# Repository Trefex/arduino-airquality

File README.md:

arduino-airquality
==================
      
In this project, we are building a mobile Arduino Fio based platform to measure air quality.

We currently have multiple components working correctly with the Arduino Fio:

- [x] GPS sensor - Adafruit Ultimate GPS Breakout v3 and the OpenLog
- [x] Dust sensor - Sharp Optical Dust Sensor
- [x] Humidity and temperature sensor - SHT10 by sensiron/DFRobot
- [x] Carbon monoxide sensor - Parallax CO sensor
- [x] Barometric pressure - BMP085 Barometric Pressure/Temperature/Altitude Sensor

We are working on combining them all into a nice light package.

Still to do:
- [x] Create circuit board sketch and etch it
- [x] Solder everything on board
- [x] Build enclosure

Next version improvements:

1. Use smaller arduino board (Nano?) potentially one with GPS builtin.

2. Decide if we want a 5V board.

3. Use 7.4V LI-ion flat and rechargeable battery pack.

4. Use only one voltage regulator if we stay with 3.3V.

5. Move voltage splitter to monitor voltage to between battery and voltage regulator.

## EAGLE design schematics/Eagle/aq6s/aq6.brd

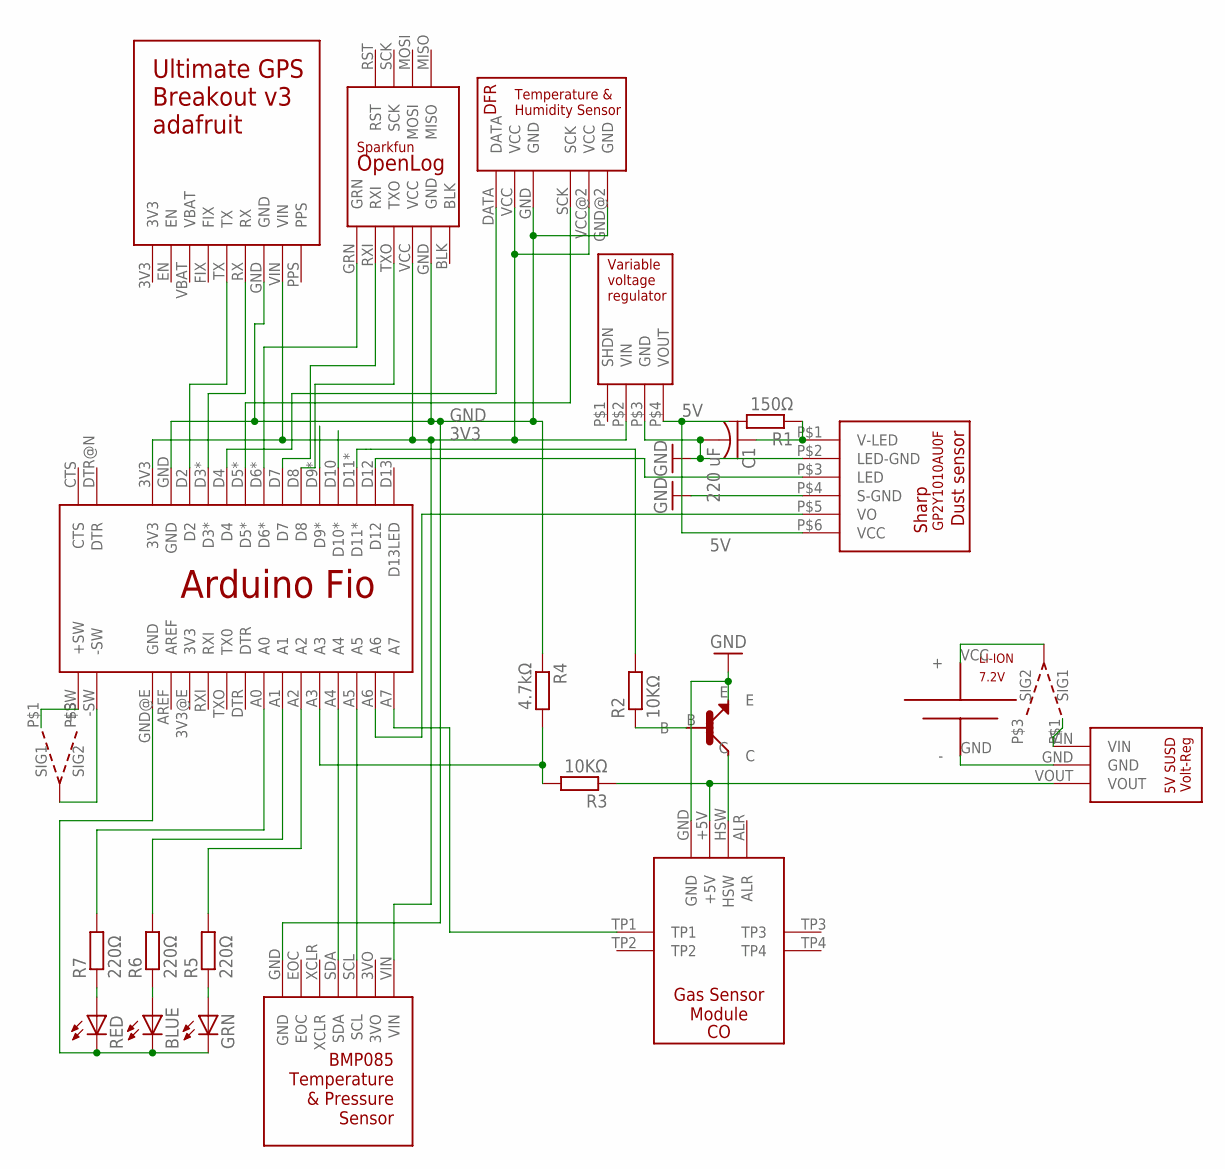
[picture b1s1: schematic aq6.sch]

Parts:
BLUE: LED5MM
C1: 220 uF; C050-025X075
CO: CO; GSM_PARALLAX
GRN: LED5MM
LI-ION: 7.2V; BATTERY_WITH_WIRE_HOLES
R1: 150Ω; 0207/15
R2, R3: 10KΩ; 0204/7
R4: 4.7kΩ; 0204/7
R5, R6, R7: 220Ω; 0204/7
RED: LED5MM
U$1: SHARP_DUST_SENSOR6PIN; 6PIN
U$2: ARDUINO_FIO
U$3: POLOLU_VAR_VOLTAGE_REG
U$4: ADAFRUIT_GPS_V3
U$5: SPARKFUN_OPENLOG
U$6: DFR_TEMP_HUMIDITY
U$7: 5V_SUSD_VOLT_REG
U$8: BMP085
U$10, U$11: SWITCH
U$12: NPN

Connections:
3V3: U$2.3V3, U$3.P$2 (VIN), U$4.VIN, U$5.VCC, U$6.VCC, U$6.VCC@2 (VCC), U$8.VIN
3VO: U$8.3VO
5V: R1.2, U$1.P$6 (VCC), U$3.P$4 (VOUT)
GND: BLUE.K (C), C1.2, CO.GND, GRN.K (C), LI-ION.GND (-), R4.1, RED.K (C), U$1.P$2 (LED-GND), U$1.P$4 (S-GND), U$2.GND, U$2.GND@E (GND), U$3.P$3 (GND), U$4.GND, U$5.GND, U$6.GND, U$6.GND@2 (GND), U$7.GND, U$8.GND, U$12.E
unnamed: U$1.P$3 (LED), U$2.D12
unnamed: C1.1, R1.1, U$1.P$1 (V-LED)
unnamed: U$1.P$5 (VO), U$2.A6
unnamed: U$2.D3*, U$4.RX
unnamed: U$2.D2, U$4.TX
unnamed: U$2.+SW, U$10.P$1 (SIG1)
unnamed: U$2.D6*, U$5.GRN
unnamed: U$2.D7, U$5.RXI
unnamed: U$2.D8, U$5.TXO
unnamed: U$2.-SW, U$10.P$2 (SIG_OUT)
unnamed: LI-ION.VCC (+), U$11.P$2 (SIG_OUT)
unnamed: U$2.D5*, U$6.SCK
unnamed: U$2.D4, U$6.DATA
unnamed: U$7.VIN, U$11.P$1 (SIG1)
unnamed: R5.2, U$2.A2
unnamed: R2.1, U$12.B
unnamed: R2.2, U$2.D11*
unnamed: CO.+5V, R3.1, U$7.VOUT
unnamed: CO.HSW, U$12.C
unnamed: CO.TP1, U$2.A7
unnamed: R3.2, R4.2, U$2.A3
unnamed: U$2.A4, U$8.SDA
unnamed: U$2.A5, U$8.SCL
unnamed: R7.2, U$2.A0
unnamed: R6.2, U$2.A1
unnamed: R7.1, RED.A
unnamed: BLUE.A, R6.1
unnamed: GRN.A, R5.1

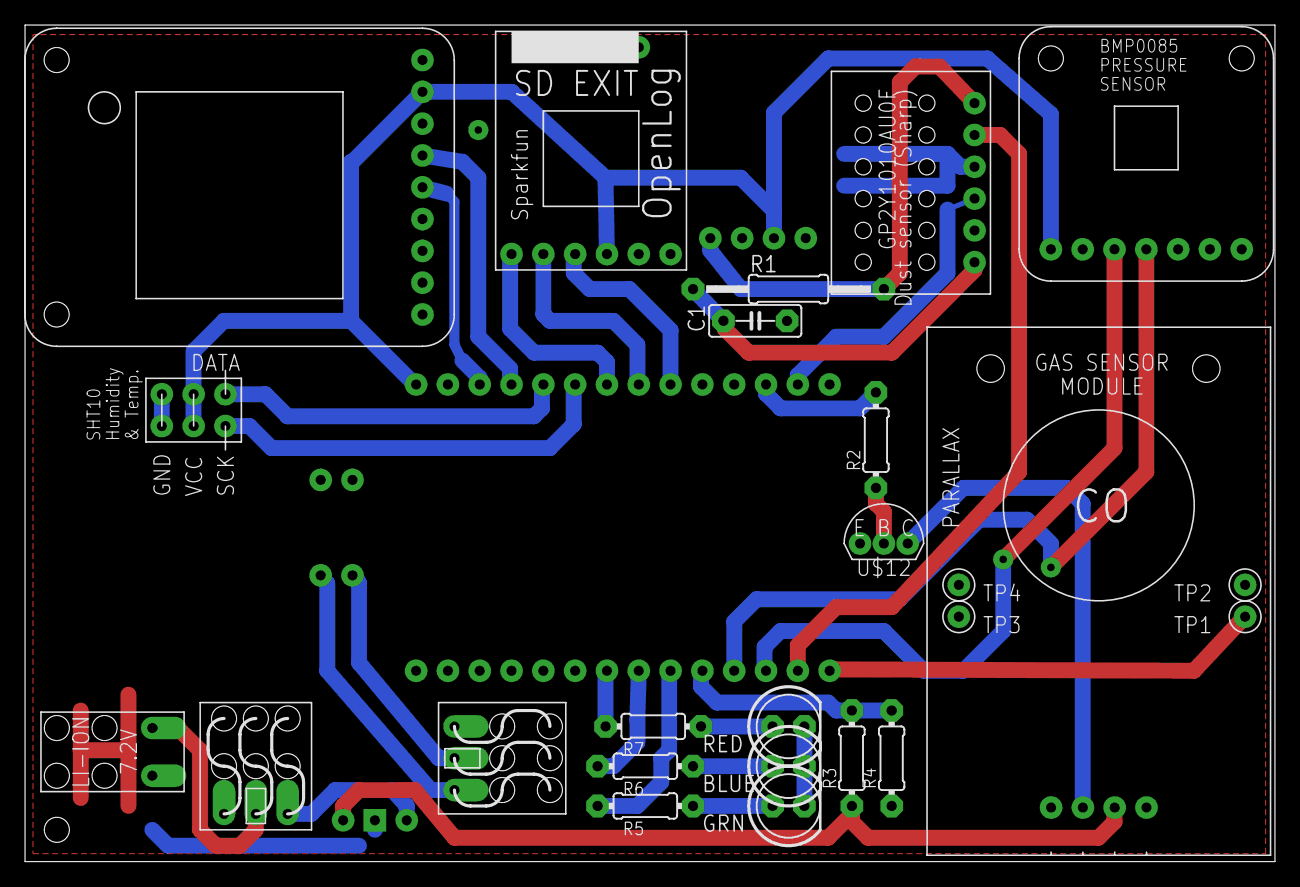
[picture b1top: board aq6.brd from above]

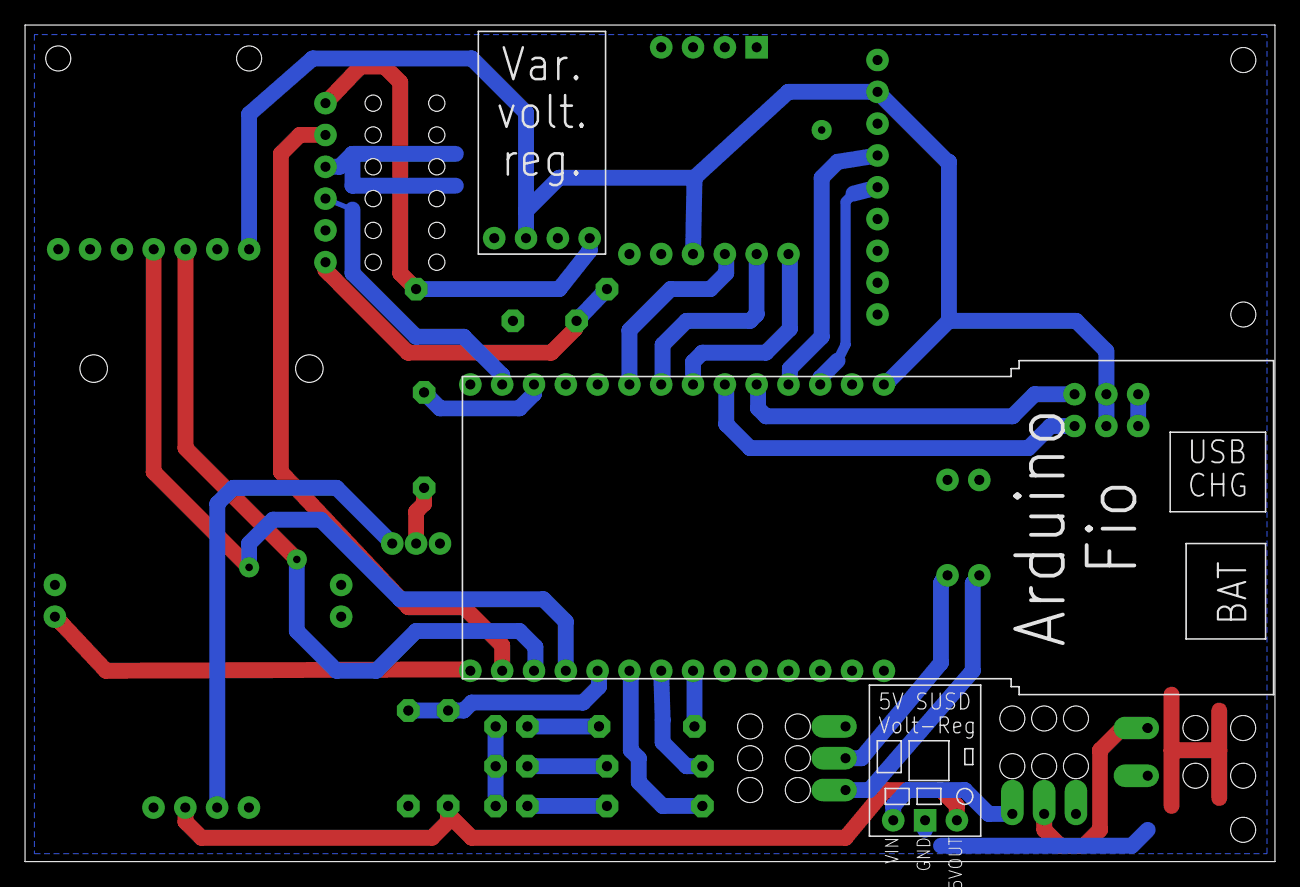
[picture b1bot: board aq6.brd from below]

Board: 2 copper layers, 99.8 x 66.8 mm, 24 parts (3 on the bottom side), 31 nets.

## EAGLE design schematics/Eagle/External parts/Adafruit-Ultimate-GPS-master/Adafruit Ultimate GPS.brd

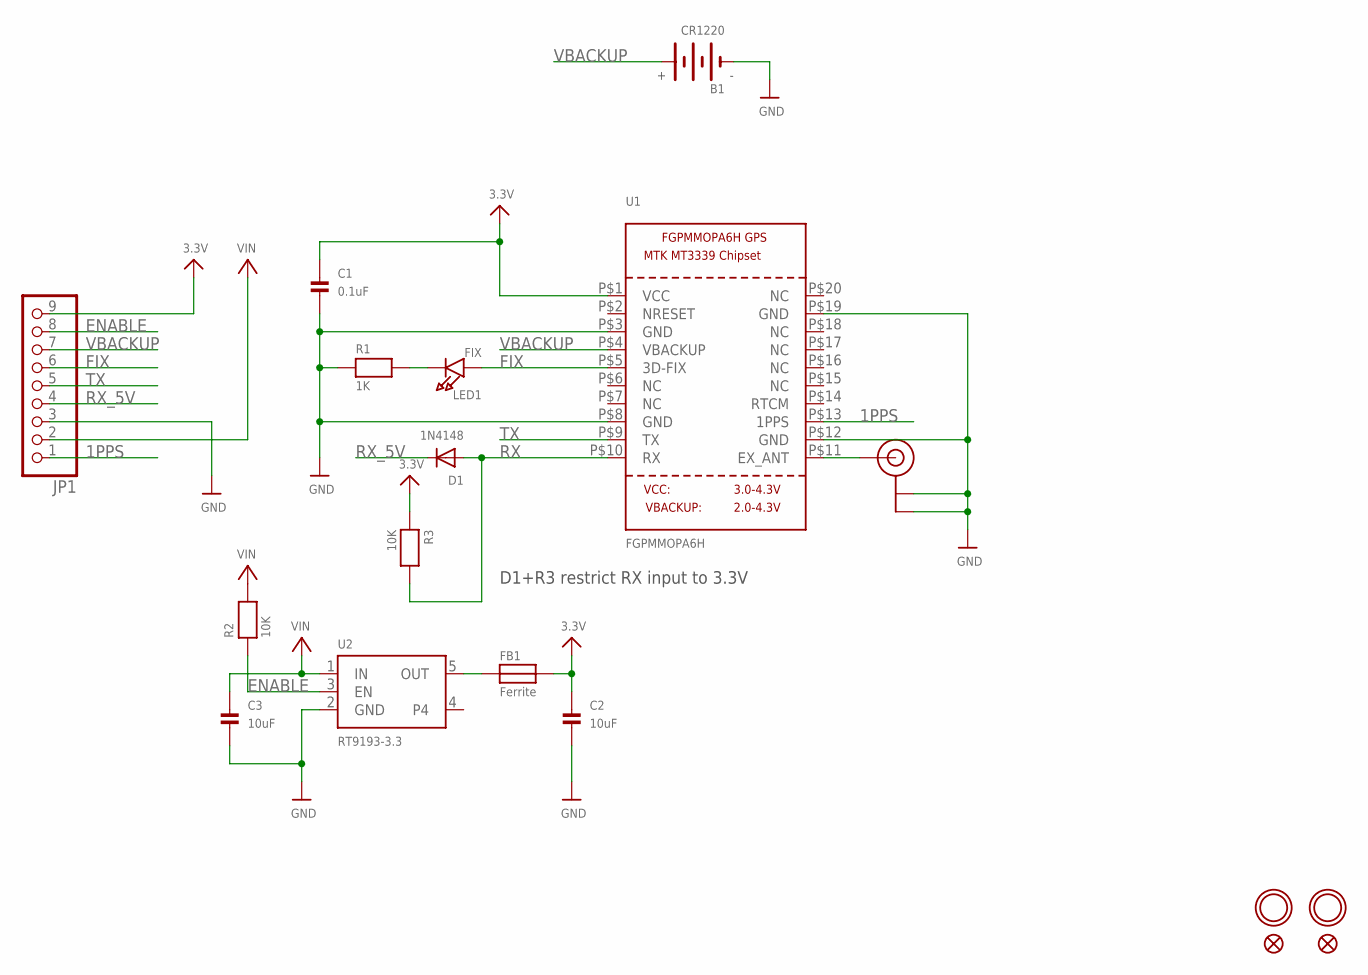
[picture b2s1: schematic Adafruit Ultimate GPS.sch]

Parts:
B1: CR1220
C1: 0.1uF; 0805
C2, C3: 10uF; 0805
D1: 1N4148; SOD-323F
FB1: Ferrite; 0805
FID1, FID2: FIDUCIAL""; FIDUCIAL_1MM
JP1: HEADER-1X970MIL; 1X09_ROUND_70
LED1: FIX; CHIPLED_0805
R1: 1K; 0805
R2, R3: 10K; 0805
U1: FGPMMOPA6H
U2: RT9193-3.3; SOT23-5
U$8, U$9: MOUNTINGHOLE2.0; MOUNTINGHOLE_2.0_PLATED
U$20: U.FL

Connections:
1PPS: JP1.1, U1.P$13 (1PPS)
3.3V: C1.1, C2.1, FB1.2, JP1.9, R3.1, U1.P$1 (VCC)
ENABLE: JP1.8, R2.1, U2.3 (EN)
FIX: JP1.6, LED1.A, U1.P$5 (3D-FIX)
GND: B1.-, C1.2, C2.2, C3.2, JP1.3, R1.1, U1.P$3 (GND), U1.P$8 (GND), U1.P$12 (GND), U1.P$19 (GND), U2.2 (GND), U$20.P$1 (GND), U$20.P$2 (GND)
unnamed: LED1.C, R1.2
unnamed: FB1.1, U2.5 (OUT)
unnamed: U1.P$11 (EX_ANT), U$20.P$3 (SIGNAL)
RX: D1.A, R3.2, U1.P$10 (RX)
RX_5V: D1.C, JP1.4
TX: JP1.5, U1.P$9 (TX)
VBACKUP: B1.+$1 (+), JP1.7, U1.P$4 (VBACKUP)
VIN: C3.1, JP1.2, R2.2, U2.1 (IN)

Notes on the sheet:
D1+R3 restrict RX input to 3.3V

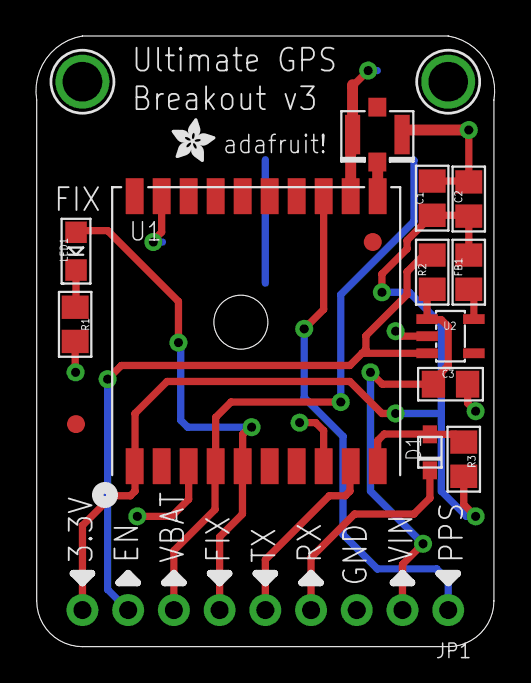
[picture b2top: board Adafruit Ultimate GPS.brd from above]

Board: 2 copper layers, 25.5 x 33.9 mm, 19 parts (1 on the bottom side), 13 nets.

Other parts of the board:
U$15: ADAFRUIT_2.5MM

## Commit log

2012-12-01 - Initial Import of CO Sensor Module Project and Documentation
2012-12-01 Initial commit of the GPD Module project folder and documentation
2012-12-01 Fixed sensor type
2012-12-01 Added Assembly sketch for Dust Sensor w/ Arduino Fio
2012-12-01 Changed folder name to assembly
2012-12-01 Updated Module_Dust-Sensor/README.md
2012-12-01 Smaller sketch image for the rendering of Readme.MD
2012-12-01 Cleaned up code Add example output data
2012-12-01 Example output was taken with 5V Arduino Uno
2012-12-13 - Converted mg/m3 to ug/m3 which seems to be the accepted standard - Added images from the Blog - Added output for airquality sensor with the Fio
2012-12-16 - Initial commit of Dust Sensor + OpenLog + Adafruit GPS
2012-12-16 - Initial Import. Code needs serious cleanup
2012-12-17 - Cleaned up code - Added Barometric Sensor but not used in this code
2013-03-09 Added the humidity-temp module, updated main README
2013-03-09 Updated README.md again
2013-03-16 - Addition of Barometer sensor
2013-03-16 added libraries
2013-03-16 Created the new folder holding the 5 sensors and libraries all together Code compiles successfully!
2013-03-16 Updated the humidity-temp module to work out of the box: - updated file names - moved them around - updated readme/changes - set #include path to relative - no longer need to move anything to the lib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
2013-03-16 Deleted old humidity-temp directory
2013-10-16 Have the 5 sensors working together correctly"
2013-10-19 - Added library for MQ-7
2013-10-19 - Updated comments
2013-10-19 - Added datashet for Parallax
2013-11-16 cleaned redundant files
2013-11-27 first attempt - not working, wiring has logic problems?
2013-11-29 Corrected code but NPN connection not working correctly - always on
2013-11-30 Works after joining both power supply grounds
2013-12-01 Added proper header and licensing information
2013-12-01 Added idea for additional sensors
2013-12-01 Rename faulty filename
2013-12-21 Finished CO code with PWM
2013-12-22 added some analysis stuff and cleaned ino
2013-12-22 more little changes?
2013-12-22 - Initial Import of CO Sensor Module Added - Untested code
2013-12-22 - Fixed small bug around CO code
2013-12-23 Uses pin 13 to indicate if heating the coil
2013-12-23 added voltage monitoring to circuit
2014-01-04 Updated CitizSensor library, bugs in sketch
2014-01-04 cleaned up
2014-01-05 Updated CO_Sensor to use new library
2014-01-10 fixed cycle state bug
2014-01-11 Cleanup up.
2014-01-11 Added CO lib.
2014-01-11 Removed old CO code and added library code instead
2014-01-11 Fixed pin for CO
2014-01-11 Updated comments
2014-01-11 Added libraries and CO stats
2014-01-11 Updated to use BMP library v2 and Adafruit USD
2014-01-11 little fixes
2014-01-26 CO working, Logger not working - GPS conv. prob?
2014-01-26 Added some doc, config, outputs
2014-01-26 aqs6 output
2014-01-29 Minor changes to GPS printouts and OpenLog messages
2014-02-06 Added new OpenLog debugging ino and aq6s code
2014-02-09 Fixed OpenLog problems due to dust sensor, cleaned Breadboard
2014-02-15 Added initial purge duration option to constructor
2014-02-15 Updated CO library and ino code
2014-02-18 Updated CO_sensor, added mux status leds
2014-02-19 Update README.md
    Updated our to do list and completed tasks.
2014-02-19 Update README.md
    Clarification, simplification
2014-02-19 Update README.md
    Added Barometric sensor reference
2014-02-24 Created PCB schematic in fritzing , needs custom components.
2014-03-05 Cleaned up code, comments for SHT10 module to sync with blog post
2014-03-21 Updated PCB, need to update pins in code!
2014-03-24 Created first PCB draft design, pins have changed! Update code!
2014-03-27 Finished fritzing PCB, don't like it. Started Eagle cad PCB.
2014-03-30 Added more components to Eagle schematic, library
2014-03-31 Finished circuit diagram, needs checking
2014-04-05 PCB layout tentatively ok, routing next
2014-04-09 PCB first draft, needs checking and adjustment
2014-05-02 Removed mux/bit shift register
2014-05-03 Thickened pcd traces
2014-05-05 pcb images
2014-05-05 pcb first etch design
2014-05-15 Fixed pcb, reexport to png! Update Ard. code
2014-05-15 Updated pcb images: bottom, top
2014-05-17 pcb and code updates
2014-05-28 Updated arduino code
2014-05-30 Changed pins, fixed CO reporting - Logger not working
2014-06-14 Edited battery holder, flexibility and length
2014-06-14 Added 3d model files - need to print gcode
2014-06-22 Edited battery, code - v1?
2016-12-16 Fixed formatting
2019-02-25 test
